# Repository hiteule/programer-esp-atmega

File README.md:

# ESP / Atmega programmer

An electronic board designed to programm an ESP or an Atmega microcontroller.
The board is based on a FT32RL Serial Adapter module.

You need to switch the JP-RTS jumper to be able to programm the ESP or the Atmega.
You need to switch the voltage level of the Serial Adapter module to programm the ESP (3.3V) or the Atmega (5V).

The 3.3V power output of the Serial Adapter module is too weak to run the ESP.
You need to use an external power source between 3.3V and 12V through J1.
The Atmega is not concerned (powered through the USB / Serial Adapter module).

The card was designed with [Eagle].
The additional [libraries] used are:
* CONNECTORS.lbr
* regulator.lbr

[Eagle]:     https://www.autodesk.fr/products/eagle
[libraries]: https://github.com/hiteule/eagle-library

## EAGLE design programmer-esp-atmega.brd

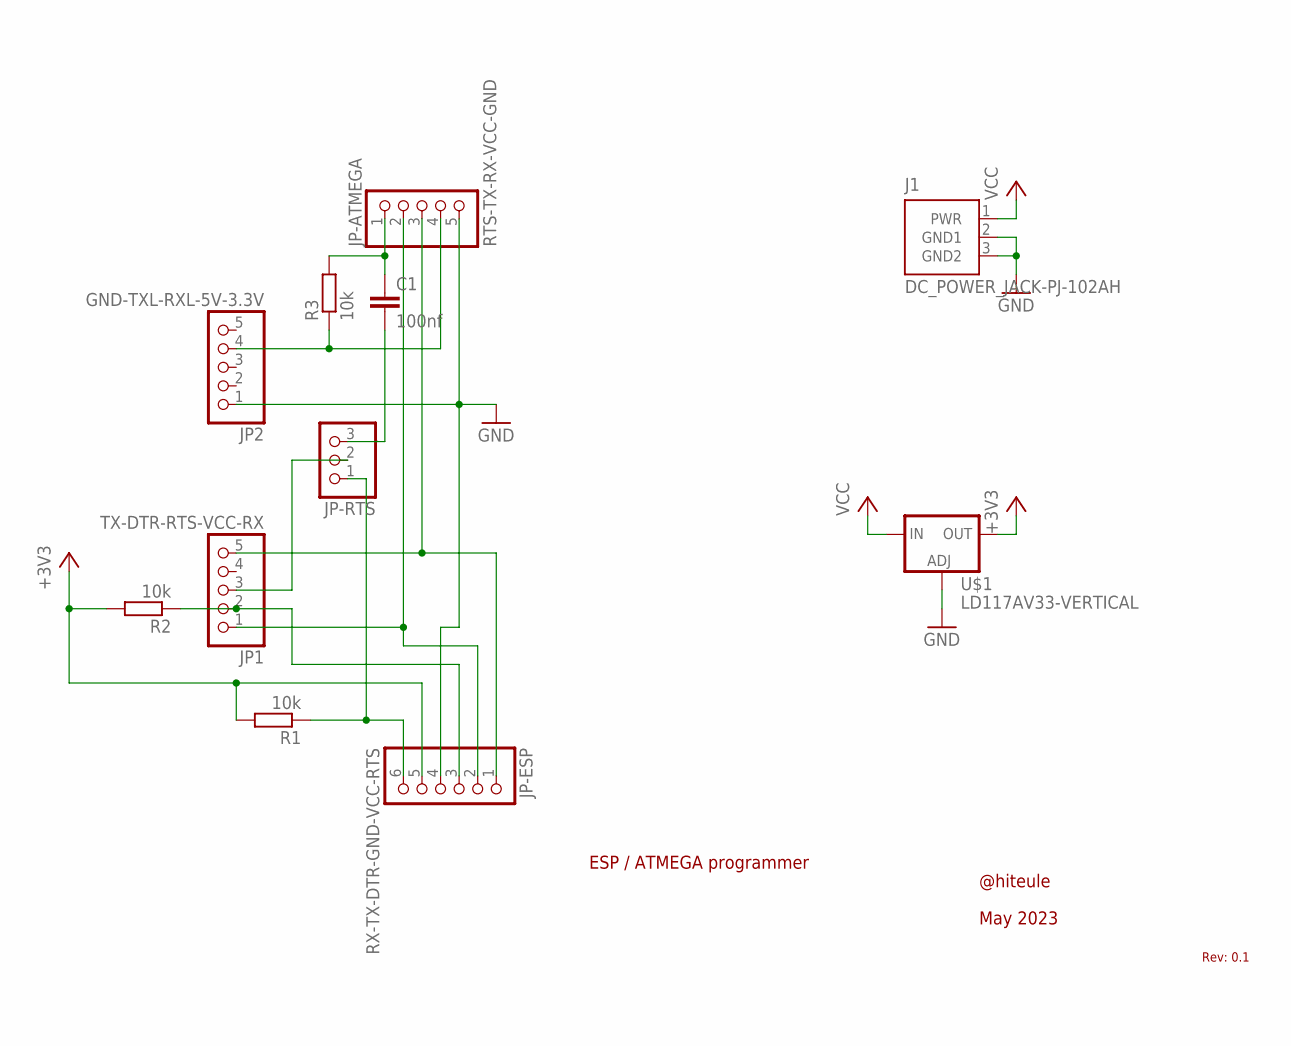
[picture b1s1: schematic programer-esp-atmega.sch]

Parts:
C1: 100nf; C025-024X044
J1: DC_POWER_JACK-PJ-102AH; PJ-102AH
JP1: TX-DTR-RTS-VCC-RX; 1X05
JP2: GND-TXL-RXL-5V-3.3V; 1X05
JP-ATMEGA: RTS-TX-RX-VCC-GND; 1X05
JP-ESP: RX-TX-DTR-GND-VCC-RTS; 1X06
JP-RTS: PINHD-1X3; 1X03
R1, R2, R3: 10k; 0207/10
U$1: LD117AV33-VERTICAL; TO220S-VERTICAL

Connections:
+3V3: JP-ESP.5, R1.2, R2.2, U$1.2 (OUT)
GND: J1.2 (GND1), J1.3 (GND2), JP2.1, JP-ATMEGA.5, JP-ESP.4, U$1.1 (ADJ)
unnamed: JP2.4, JP-ATMEGA.4, R3.1
unnamed: JP1.5, JP-ATMEGA.3, JP-ESP.1
unnamed: JP1.1, JP-ATMEGA.2, JP-ESP.2
unnamed: C1.2, JP-RTS.3
unnamed: C1.1, JP-ATMEGA.1, R3.2
unnamed: JP1.3, JP-RTS.2
unnamed: JP-ESP.6, JP-RTS.1, R1.1
unnamed: JP1.2, JP-ESP.3, R2.1
VCC: J1.1 (PWR), U$1.3 (IN)

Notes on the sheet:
ESP / ATMEGA programmer
@hiteule
May 2023
Rev: 0.1

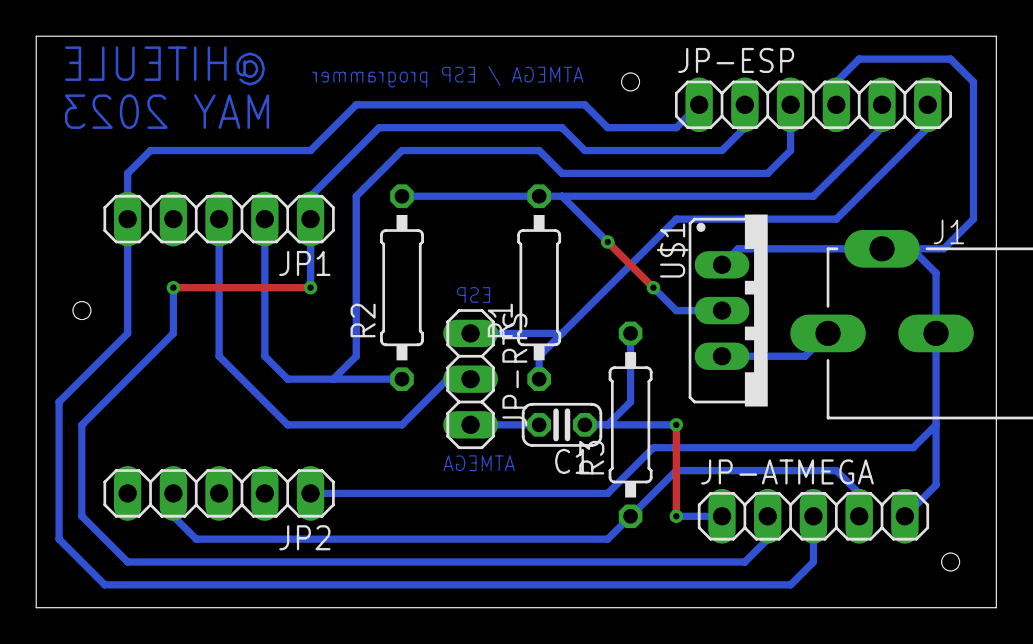
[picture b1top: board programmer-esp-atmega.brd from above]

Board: 2 copper layers, 53.3 x 31.8 mm, 11 parts (0 on the bottom side), 11 nets.

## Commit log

2023-05-27 oups, files renaming
